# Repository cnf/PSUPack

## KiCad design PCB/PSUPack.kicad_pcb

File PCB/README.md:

# PSUPack PCB

[KiCanvas](https://kicanvas.org/?github=https%3A%2F%2Fgithub.com%2Fcnf%2FPSUPack%2Ftree%2Fmain%2FPCB)

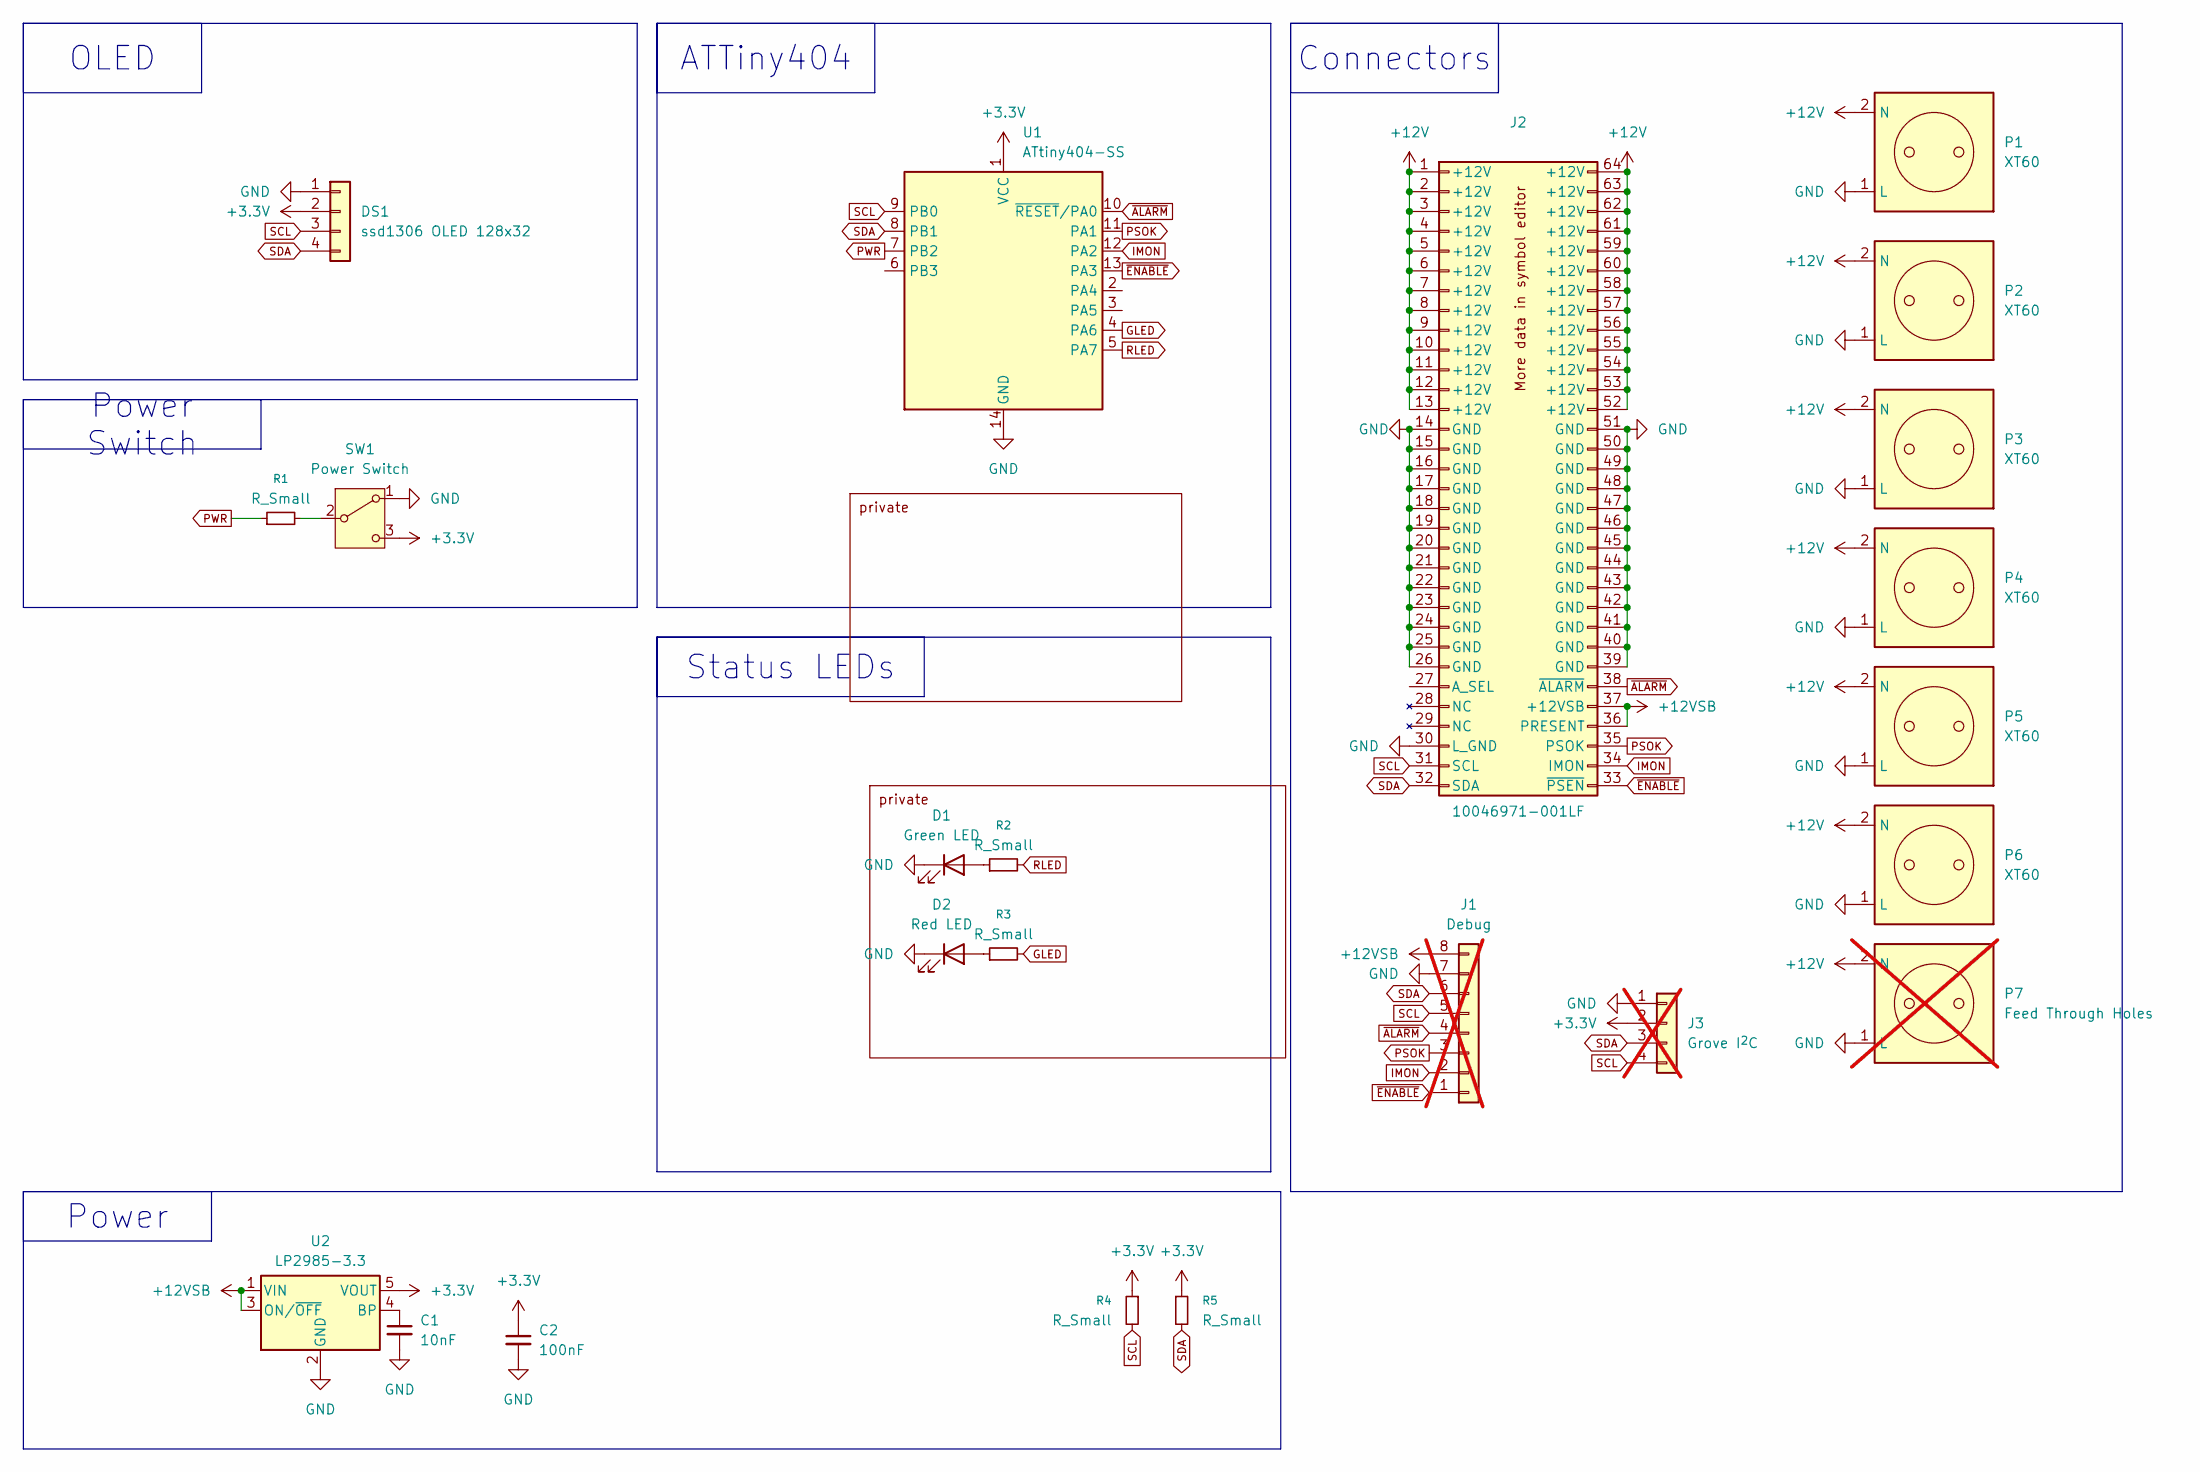
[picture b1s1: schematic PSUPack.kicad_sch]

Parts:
C1: 10nF; C_0805_2012Metric
C2: 100nF; C_0805_2012Metric
D1: Green LED; LED_0805_2012Metric
D2: Red LED; LED_0805_2012Metric
DS1: ssd1306 OLED 128x32; PinHeader_1x04_P2.54mm_Vertical
J1: Debug; PinSocket_1x08_P1.27mm_Vertical; not fitted
J2: 10046971-001LF; CONN_10046971-001LF_AMP
J3: Grove I^{2}C; NS-Tech_Grove_1x04_P2mm_Vertical; not fitted
P1, P2, P3, P4, P5, P6: XT60; AMASS_XT60-F_1x02_P7.20mm_Vertical
P7: Feed Through Holes; AMASS_XT60-F_1x02_P7.20mm_Vertical; not fitted
R1, R2, R3, R4, R5: R_Small; R_0805_2012Metric_Pad1.15x1.40mm
SW1: Power Switch; SW_Slide_SPDT_Straight_CK_OS102011MS2Q
U1: ATtiny404-SS; SOIC-14_3.9x8.7mm_P1.27mm
U2: LP2985-3.3; SOT-23-5

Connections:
+3.3V: C2.1, DS1.2, J3.2, R4.1, R5.1, SW1.3 (C), U1.1 (VCC), U2.5 (VOUT)
+12V: J2.1 (+12V), J2.2 (+12V), J2.3 (+12V), J2.4 (+12V), J2.5 (+12V), J2.6 (+12V), J2.7 (+12V), J2.8 (+12V), J2.9 (+12V), J2.10 (+12V), J2.11 (+12V), J2.12 (+12V), J2.13 (+12V), J2.52 (+12V), J2.53 (+12V), J2.54 (+12V), J2.55 (+12V), J2.56 (+12V), J2.57 (+12V), J2.58 (+12V), J2.59 (+12V), J2.60 (+12V), J2.61 (+12V), J2.62 (+12V), J2.63 (+12V), J2.64 (+12V), P1.2 (N), P2.2 (N), P3.2 (N), P4.2 (N), P5.2 (N), P6.2 (N), P7.2 (N)
+12VSB: J1.8, J2.36 (PRESENT), J2.37 (+12VSB), U2.1 (VIN), U2.3 (ON/~OFF)
GLED: R3.2, U1.4 (PA6)
GND: C1.2, C2.2, D1.1 (K), D2.1 (K), DS1.1, J1.7, J2.14 (GND), J2.15 (GND), J2.16 (GND), J2.17 (GND), J2.18 (GND), J2.19 (GND), J2.20 (GND), J2.21 (GND), J2.22 (GND), J2.23 (GND), J2.24 (GND), J2.25 (GND), J2.26 (GND), J2.30 (L_GND), J2.39 (GND), J2.40 (GND), J2.41 (GND), J2.42 (GND), J2.43 (GND), J2.44 (GND), J2.45 (GND), J2.46 (GND), J2.47 (GND), J2.48 (GND), J2.49 (GND), J2.50 (GND), J2.51 (GND), J3.1, P1.1 (L), P2.1 (L), P3.1 (L), P4.1 (L), P5.1 (L), P6.1 (L), P7.1 (L), SW1.1 (A), U1.14 (GND), U2.2 (GND)
IMON: J1.2, J2.34 (IMON), U1.12 (PA2)
unnamed: D1.2 (A), R2.1
unnamed: D2.2 (A), R3.1
unnamed: R1.2, SW1.2 (B)
unnamed: C1.1, U2.4 (BP)
PSOK: J1.3, J2.35 (PSOK), U1.11 (PA1)
PWR: R1.1, U1.7 (PB2)
RLED: R2.2, U1.5 (PA7)
SCL: DS1.3, J1.5, J2.31 (SCL), J3.4, R4.2, U1.9 (PB0)
SDA: DS1.4, J1.6, J2.32 (SDA), J3.3, R5.2, U1.8 (PB1)
~ALARM: J1.4, J2.38 (~ALARM), U1.10 (~RESET/PA0)
~ENABLE: J1.1, J2.33 (~PSEN), U1.13 (PA3)

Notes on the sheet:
Power
Connectors
OLED
ATTiny404
Status LEDs
Power Switch

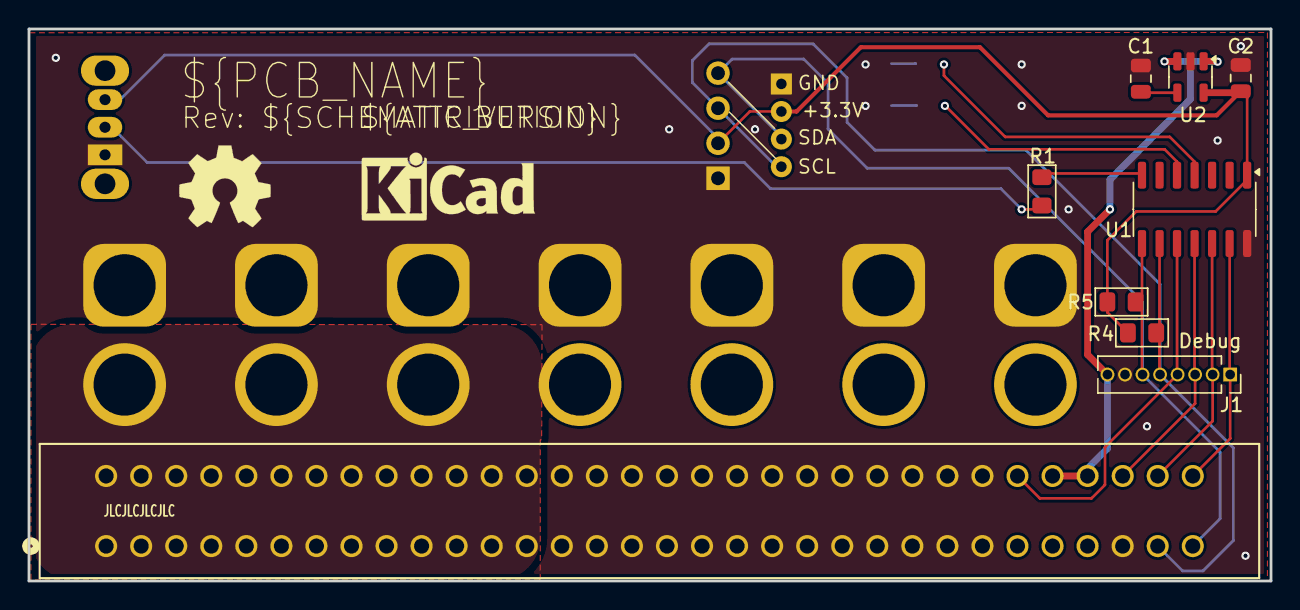
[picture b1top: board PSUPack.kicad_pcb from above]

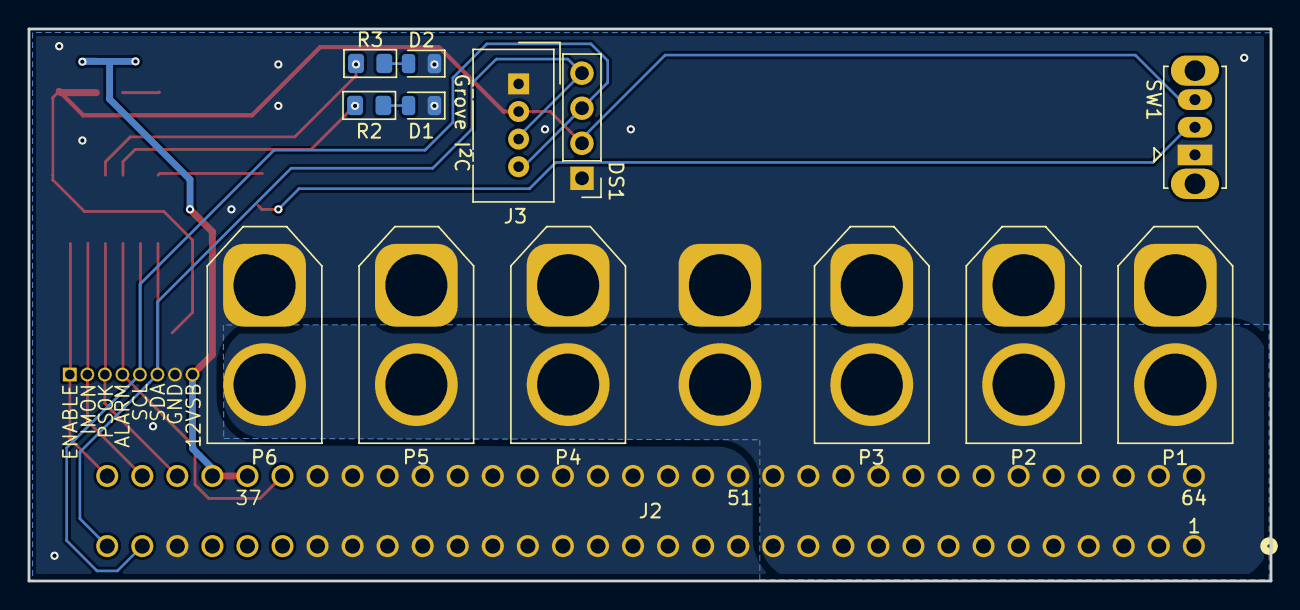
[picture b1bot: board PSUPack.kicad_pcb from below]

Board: 2 copper layers, 90.0 x 40.0 mm, 23 parts (14 on the bottom side), 17 nets.

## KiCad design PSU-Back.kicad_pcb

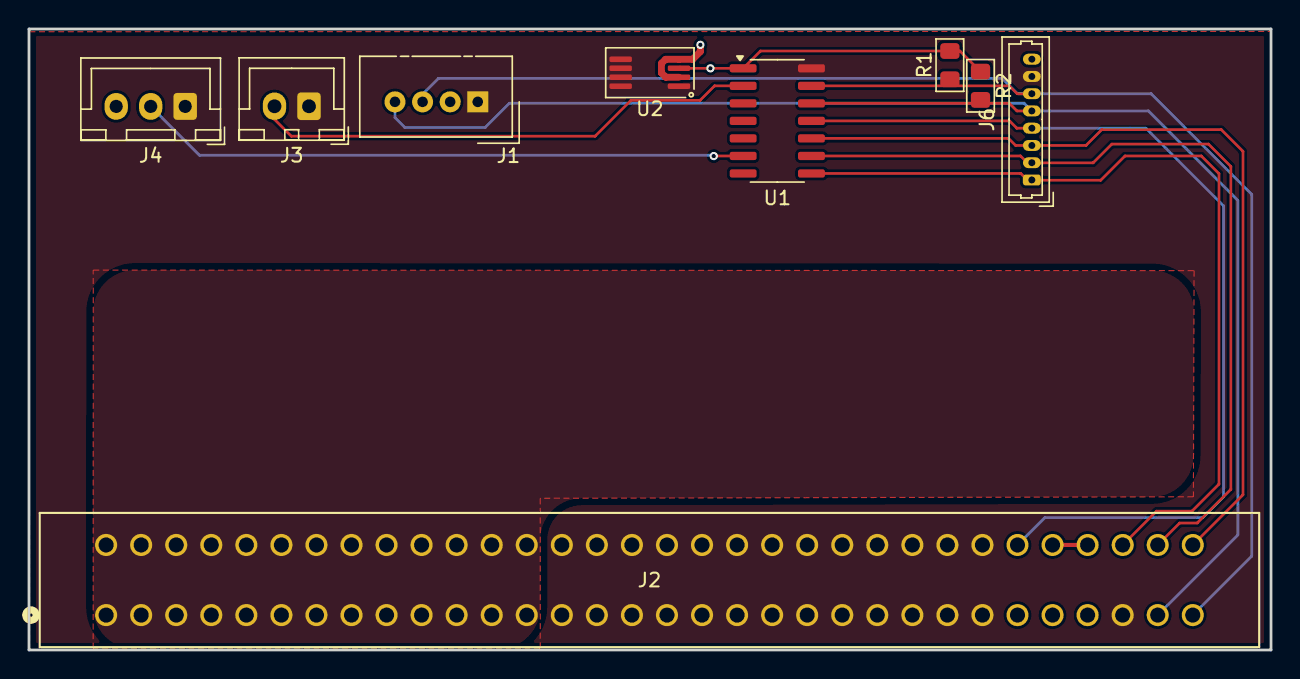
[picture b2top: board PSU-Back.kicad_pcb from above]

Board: 4 copper layers, 90.0 x 45.0 mm, 9 parts (0 on the bottom side), 12 nets.

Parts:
J1: Grove I^{2}C; NS-Tech_Grove_1x04_P2mm_Vertical
J2: 10046971-001LF; CONN_10046971-001LF_AMP
J3: PWR; JST_XH_B2B-XH-A_1x02_P2.50mm_Vertical
J4: ON; JST_XH_B3B-XH-A_1x03_P2.50mm_Vertical
J6: Conn_01x08; Molex_PicoBlade_53047-0810_1x08_P1.25mm_Vertical
R1, R2: R_Small; R_0805_2012Metric_Pad1.15x1.40mm
U1: ATtiny20-SS; SOIC-14_3.9x8.7mm_P1.27mm
U2: ADP1720ARMZ-3.3; MSOP-8_3x3mm_P0.65mm

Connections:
+3.3V: J1.2, R1.1, R2.1, U1.1 (VCC), U2.3 (OUT)
+12V: J2.1 (+12V), J2.2 (+12V), J2.3 (+12V), J2.4 (+12V), J2.5 (+12V), J2.6 (+12V), J2.7 (+12V), J2.8 (+12V), J2.9 (+12V), J2.10 (+12V), J2.11 (+12V), J2.12 (+12V), J2.13 (+12V), J2.52 (+12V), J2.53 (+12V), J2.54 (+12V), J2.55 (+12V), J2.56 (+12V), J2.57 (+12V), J2.58 (+12V), J2.59 (+12V), J2.60 (+12V), J2.61 (+12V), J2.62 (+12V), J2.63 (+12V), J2.64 (+12V)
+12VSB: J2.36 (PRESENT), J2.37 (+12VSB), J6.8, U2.2 (IN), U2.4 (EN)
GND: J1.1, J2.14 (GND), J2.15 (GND), J2.16 (GND), J2.17 (GND), J2.18 (GND), J2.19 (GND), J2.20 (GND), J2.21 (GND), J2.22 (GND), J2.23 (GND), J2.24 (GND), J2.25 (GND), J2.26 (GND), J2.30 (L_GND), J2.39 (GND), J2.40 (GND), J2.41 (GND), J2.42 (GND), J2.43 (GND), J2.44 (GND), J2.45 (GND), J2.46 (GND), J2.47 (GND), J2.48 (GND), J2.49 (GND), J2.50 (GND), J2.51 (GND), J3.1, J4.1, J6.7, U1.14 (GND), U2.1 (GND), U2.5 (GND), U2.6 (GND), U2.7 (GND), U2.8 (GND)
IMON: J2.34 (IMON), J6.2, U1.9 (PA4)
ON: J4.2, U1.6 (PA7)
PSOK: J2.35 (PSOK), J6.1, U1.8 (PA5)
PWR: J3.2, U1.2 (PB0)
SCL: J1.4, J2.31 (SCL), J6.5, R2.2, U1.12 (PA1)
SDA: J1.3, J2.32 (SDA), J6.6, R1.2, U1.13 (PA0)
~ALARM: J2.38 (~ALARM), J6.4, U1.11 (PA2)
~ENABLE: J2.33 (~PSEN), J6.3, U1.10 (PA3)

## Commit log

2025-09-04 initial
2025-09-06 license
2025-09-06 begin of firmware
2025-09-12 JLCPCB Ordered of Rev A
